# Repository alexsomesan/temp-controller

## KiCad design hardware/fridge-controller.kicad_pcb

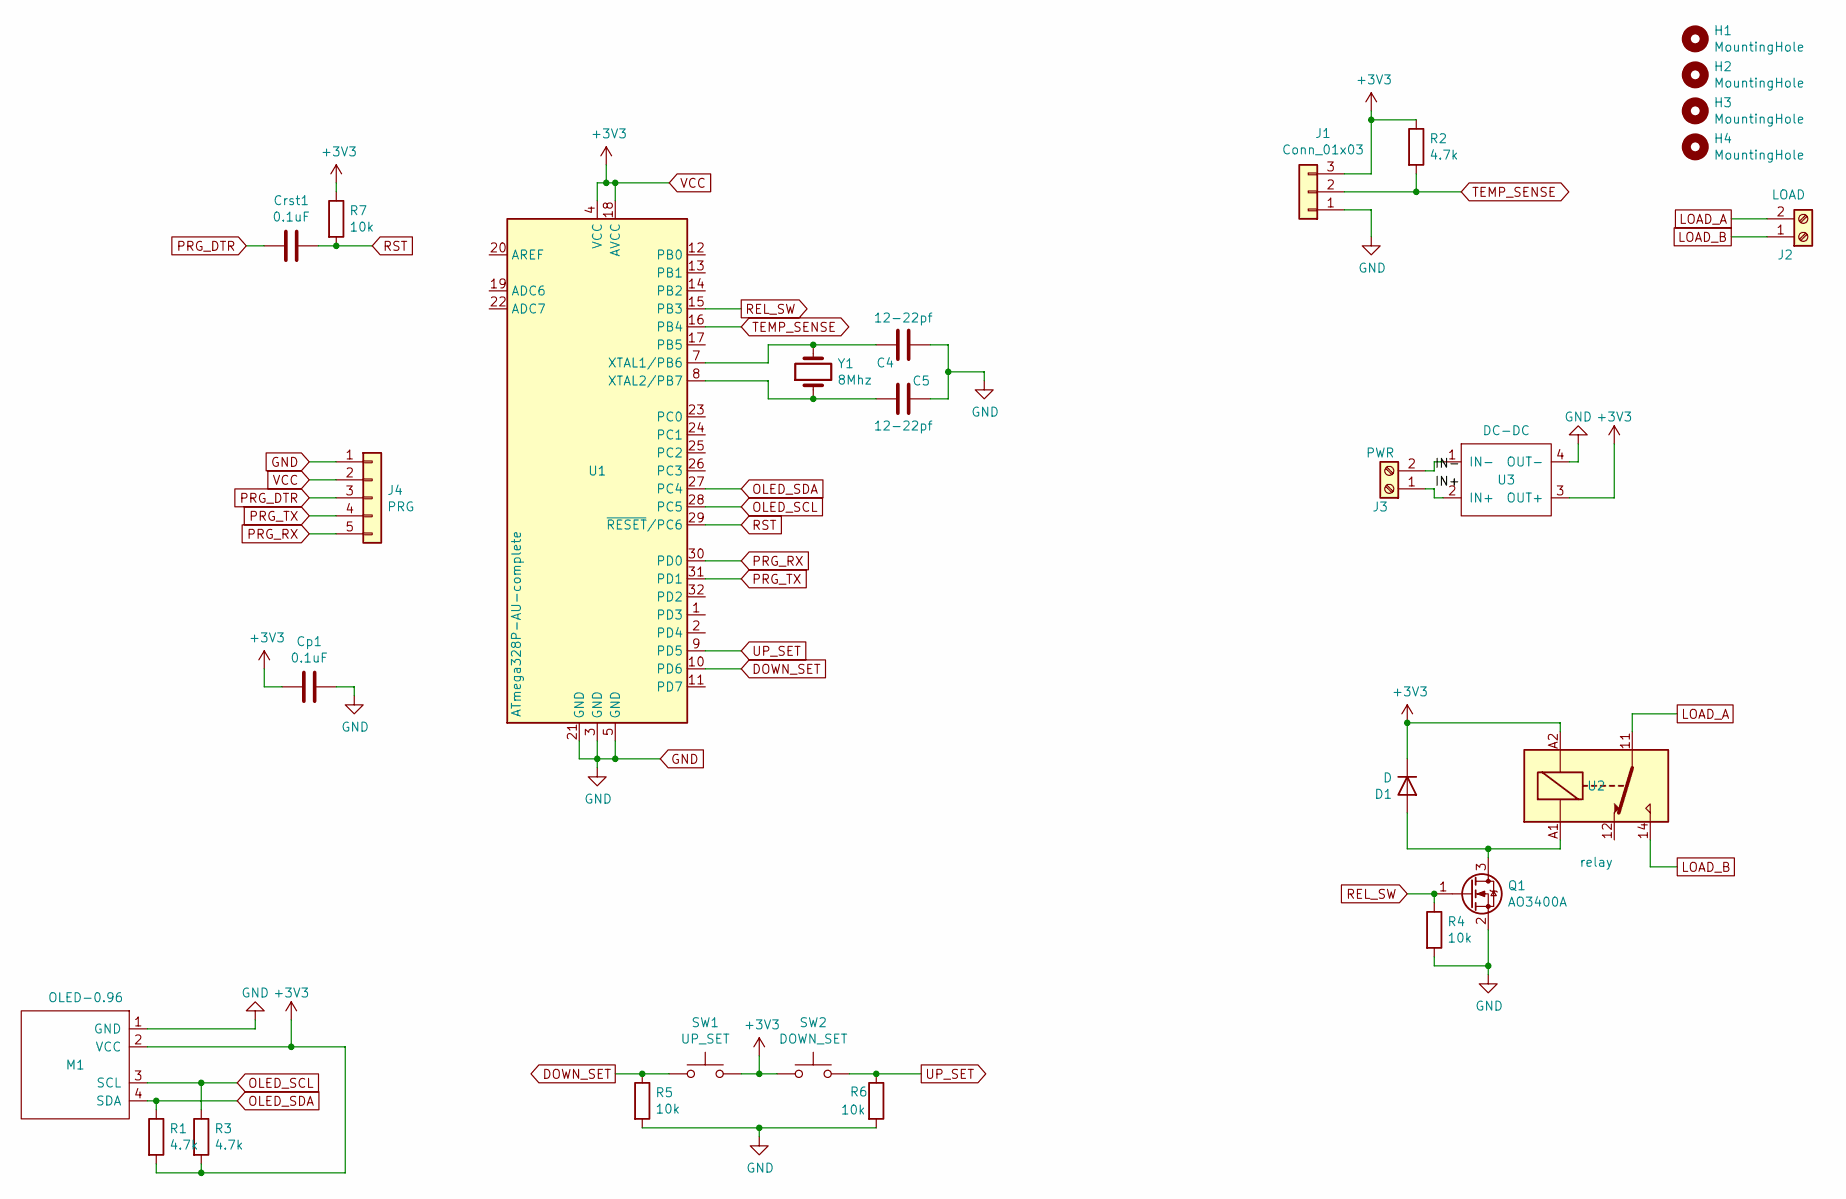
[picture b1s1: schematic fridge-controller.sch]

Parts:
C4, C5: 12-22pf; R_1206_3216Metric_Pad1.30x1.75mm_HandSolder
Cp1: 0.1uF; R_1206_3216Metric_Pad1.30x1.75mm_HandSolder
Crst1: 0.1uF; R_1206_3216Metric_Pad1.30x1.75mm_HandSolder
D1: D; R_1206_3216Metric_Pad1.30x1.75mm_HandSolder
H1, H2, H3, H4: MountingHole; MountingHole_2.1mm
J1: Conn_01x03; JST_XH_B3B-XH-A_1x03_P2.50mm_Vertical
J2: LOAD; TerminalBlock_Phoenix_PT-1,5-2-5.0-H_1x02_P5.00mm_Horizontal
J3: PWR; TerminalBlock_Phoenix_PT-1,5-2-5.0-H_1x02_P5.00mm_Horizontal
J4: PRG; PinHeader_1x05_P1.27mm_Vertical
M1: OLED-0.96
Q1: AO3400A; SOT-23
R1, R2, R3: 4.7k; R_1206_3216Metric_Pad1.30x1.75mm_HandSolder
R4, R5, R6, R7: 10k; R_1206_3216Metric_Pad1.30x1.75mm_HandSolder
SW1: UP_SET; SW_PUSH_6mm_H8mm
SW2: DOWN_SET; SW_PUSH_6mm_H8mm
U1: ATmega328P-AU-complete; TQFP-32_7x7mm_P0.8mm
U2: relay; Relay_SPDT_Finder_36.11
U3: DC-DC
Y1: 8Mhz; Crystal_HC49-4H_Vertical

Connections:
/IN+: J3.1, U3.2 (IN+)
/IN-: J3.2, U3.1 (IN-)
DOWN_SET: R5.1, SW1.1, U1.10 (PD6)
GND: C4.1, C5.1, Cp1.1, J1.1, J4.1, M1.1 (GND), Q1.2 (S), R4.2, R5.2, R6.2, U1.3 (GND), U1.5 (GND), U1.21 (GND), U3.4 (OUT-)
LOAD_A: J2.2, U2.11
LOAD_B: J2.1, U2.14
unnamed: C4.2, U1.7 (XTAL1/PB6), Y1.2
unnamed: C5.2, U1.8 (XTAL2/PB7), Y1.1
unnamed: D1.2 (A), Q1.3 (D), U2.A1
OLED_SCL: M1.3 (SCL), R3.1, U1.28 (PC5)
OLED_SDA: M1.4 (SDA), R1.1, U1.27 (PC4)
PRG_DTR: Crst1.2, J4.3
PRG_RX: J4.5, U1.30 (PD0)
PRG_TX: J4.4, U1.31 (PD1)
REL_SW: Q1.1 (G), R4.1, U1.15 (PB3)
RST: Crst1.1, R7.2, U1.29 (~RESET~/PC6)
TEMP_SENSE: J1.2, R2.2, U1.16 (PB4)
UP_SET: R6.1, SW2.1, U1.9 (PD5)
VCC: Cp1.2, D1.1 (K), J1.3, J4.2, M1.2 (VCC), R1.2, R2.1, R3.2, R7.1, SW1.2, SW2.2, U1.4 (VCC), U1.6 (VCC), U1.18 (AVCC), U2.A2, U3.3 (OUT+)

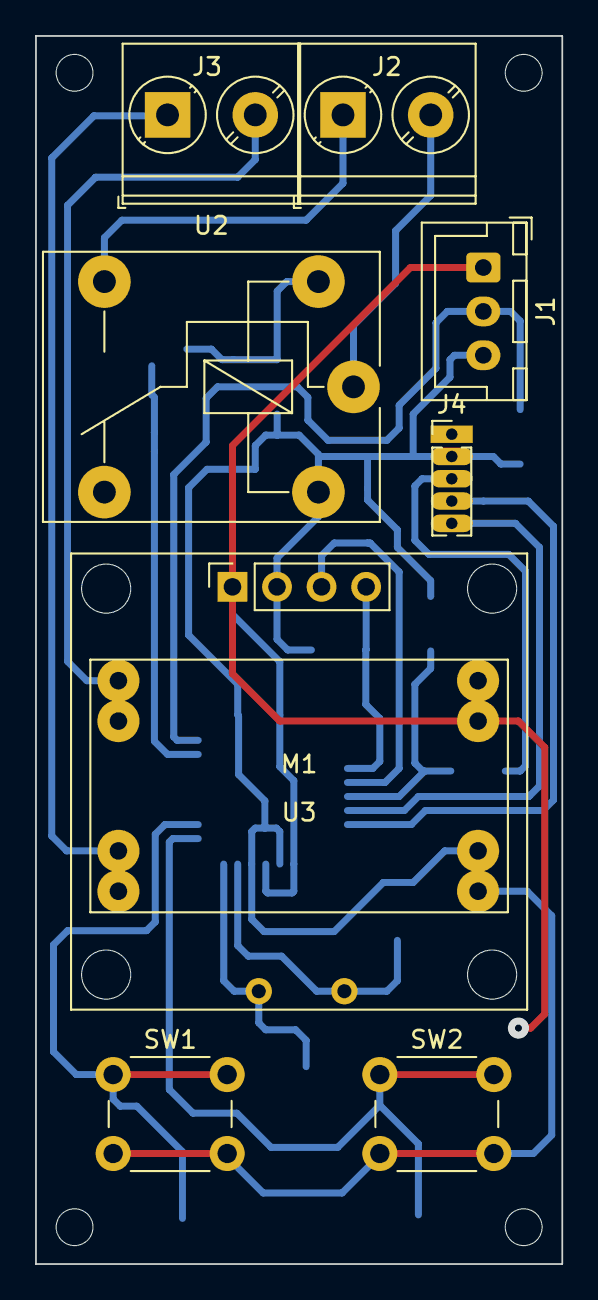
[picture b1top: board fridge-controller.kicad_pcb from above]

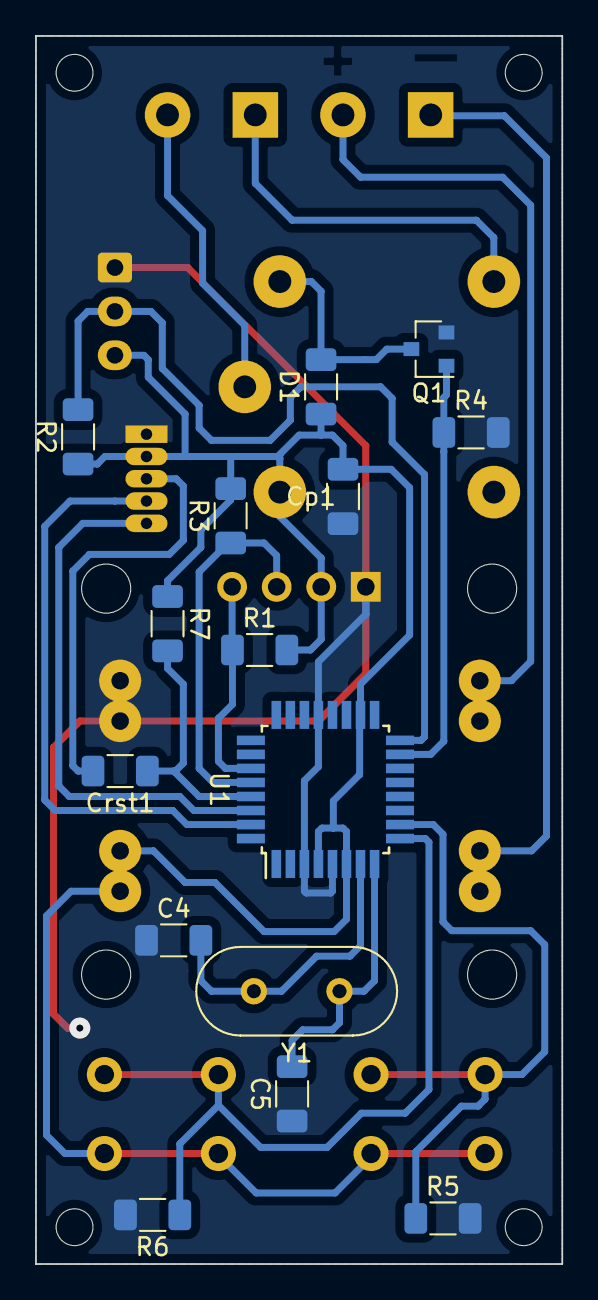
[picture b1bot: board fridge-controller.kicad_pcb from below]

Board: 2 copper layers, 30.0 x 70.0 mm, 28 parts (15 on the bottom side), 19 nets.

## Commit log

2021-07-30 working prototype
2021-07-30 simplify platformio.ini
2021-07-30 default setpoint to 4 & cleanup
2021-08-09 Handle button inputs & save to EEPROM
2021-08-09 Combine hardware and firmware
2021-08-09 Update temp every 3 seconds & check eeprom read validity
2021-08-09 Optimize buttons responsiveness
